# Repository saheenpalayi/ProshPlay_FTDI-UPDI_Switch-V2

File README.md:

# ProshPlay_FTDI-UPDI_Switch-V2

## UPDI Circuit

## 6 pin output UPDI/UART config

## Schematic

## PCB LayOut

## 3D Output

## Reference
-

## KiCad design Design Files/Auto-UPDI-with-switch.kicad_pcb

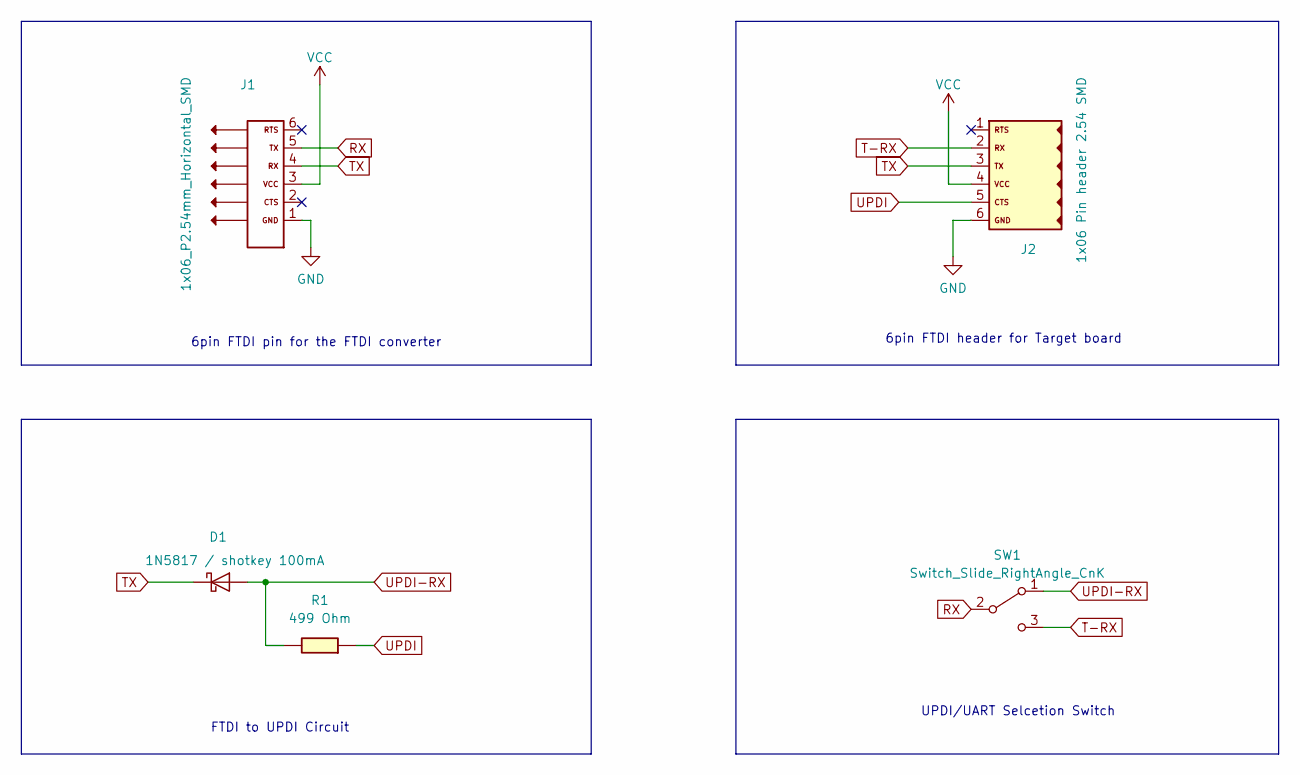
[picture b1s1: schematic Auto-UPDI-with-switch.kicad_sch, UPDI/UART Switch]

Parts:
D1: 1N5817 / shotkey 100mA; Diode_Schottky_MiniSMA
J1: 1x06_P2.54mm_Horizontal_SMD; PinHeader_1x06_P2.54mm_Horizontal_SMD
J2: 1x06 Pin header 2.54 SMD; PinSocket_1x06_P2.54mm_Horizontal_SMD
R1: 499 Ohm; R_1206
SW1: Switch_Slide_RightAngle_CnK; Switch_Slide_RightAngle_CnK_AYZ0102AGRLC_7.2x3mm

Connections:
GND: J1.1, J2.6
RX: J1.5, SW1.2 (B)
T-RX: J2.2, SW1.3 (C)
TX: D1.1 (K), J1.4, J2.3
UPDI: J2.5, R1.2
UPDI-RX: D1.2 (A), R1.1, SW1.1 (A)
VCC: J1.3, J2.4

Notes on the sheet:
6pin FTDI pin for the FTDI converter
UPDI/UART Selcetion Switch
6pin FTDI header for Target board
FTDI to UPDI Circuit

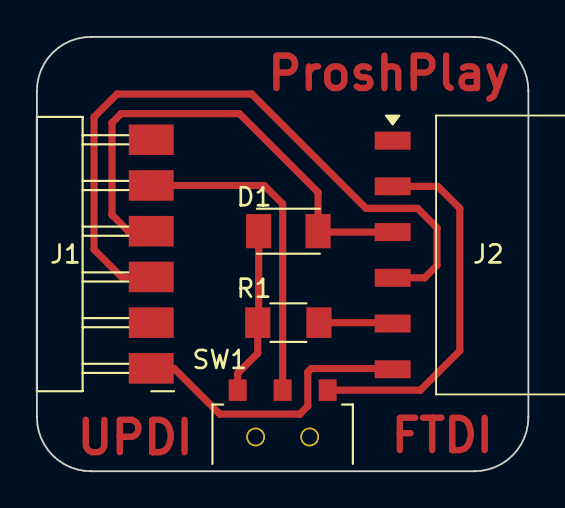
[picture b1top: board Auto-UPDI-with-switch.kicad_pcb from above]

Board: 2 copper layers, 27.3 x 24.1 mm, 5 parts (0 on the bottom side), 7 nets.

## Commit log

2025-05-12 added design files
2025-05-14 added files and updated readme
